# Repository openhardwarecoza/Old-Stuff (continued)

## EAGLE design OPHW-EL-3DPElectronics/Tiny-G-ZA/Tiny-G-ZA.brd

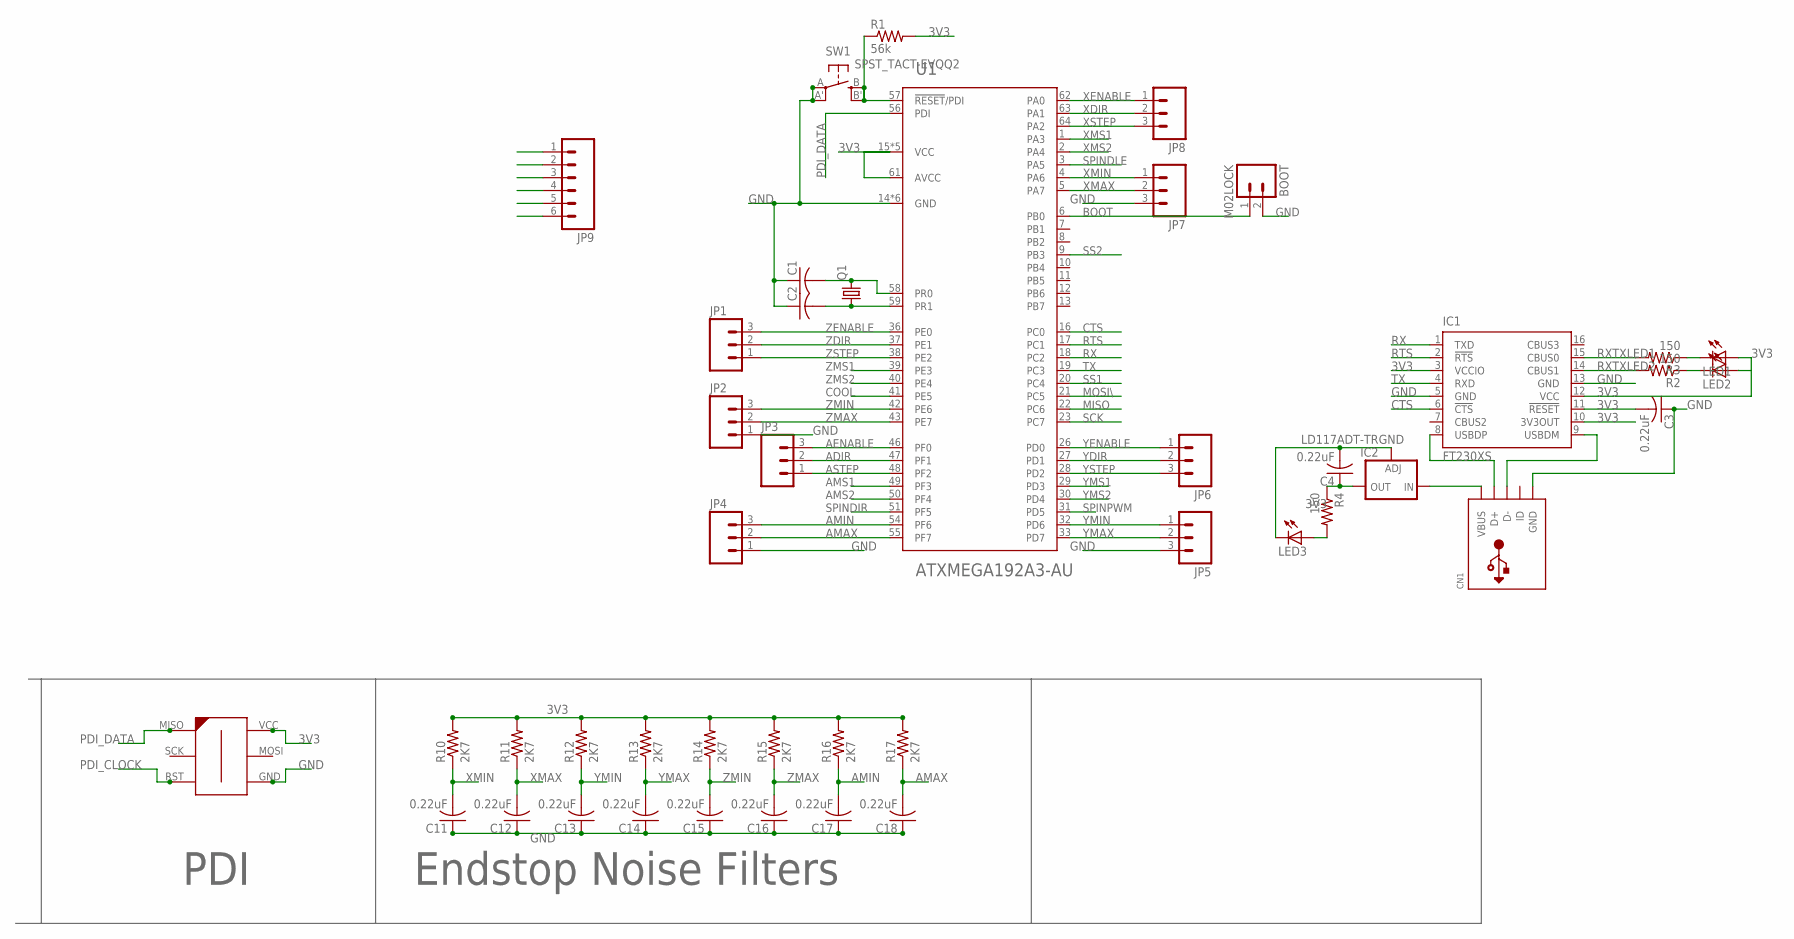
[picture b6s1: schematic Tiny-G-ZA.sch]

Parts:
BOOT: M02LOCK; 1X02_LOCK
C1, C2: C-USC1206K; C1206K
C3, C4, C11, C12, C13, C14, C15, C16, C17, C18: 0.22uF; C1206K
CN1: USBMINIB; USB-MINIB
IC1: FT230XS; SSOP16
IC2: LD117ADT-TR; DPACK
JP1, JP2, JP3, JP4, JP5, JP6, JP7, JP8: M03LONGPADS; 1X03_LONGPADS
JP9: M06LONGPADS; 1X06_LONGPADS
LED1, LED2, LED3: LEDSMT1206; 1206
Q1: CRYSTALHC49UP; HC49UP
R1: 56k; M1206
R2, R3, R4: 150; M1206
R10, R11, R12, R13, R14, R15, R16, R17: 2K7; M1206
SW1: SPST_TACT-EVQQ2; EVQ-Q2
U1: ATXMEGA192A3-AU; TQFP-64A-64
U$1: AVR-ISP-6-EDGE; 6PAD_ISP

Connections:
3V3: C3.2, C4.1, IC1.3 (VCCIO), IC1.10 (3V3OUT), IC1.11 (!RESET), IC1.12 (VCC), IC2.4 (OUT), JP9.1, LED1.A, LED2.A, R1.2, R4.1, R10.2, R11.2, R12.2, R13.2, R14.2, R15.2, R16.2, R17.2, U1.15 (VCC), U1.25 (VCC), U1.35 (VCC), U1.45 (VCC), U1.53 (VCC), U1.61 (AVCC), U$1.VCC
5V: CN1.VBUS, IC2.3 (IN)
ADIR: JP3.2, U1.47 (PF1)
AENABLE: JP3.3, U1.46 (PF0)
AMAX: C18.2, JP4.2, R17.1, U1.55 (PF7)
AMIN: C17.2, JP4.3, R16.1, U1.54 (PF6)
AMS1: U1.49 (PF3)
AMS2: U1.50 (PF4)
ASTEP: JP3.1, U1.48 (PF2)
BOOT: BOOT.1, U1.6 (PB0)
COOL: JP9.6, U1.41 (PE5)
CTS: IC1.6 (!CTS), U1.16 (PC0)
GND: BOOT.2, C1.1, C2.1, C3.1, C4.2, C11.1, C12.1, C13.1, C14.1, C15.1, C16.1, C17.1, C18.1, CN1.GND, IC1.5 (GND), IC1.13 (GND), IC2.1 (ADJ), JP2.1, JP4.1, JP5.3, JP7.3, JP9.2, LED3.C, SW1.A, SW1.A' (P1), U1.14 (GND), U1.24 (GND), U1.34 (GND), U1.44 (GND), U1.52 (GND), U1.60 (GND), U$1.GND
MISO: U1.22 (PC6)
MOSI\: U1.21 (PC5)
unnamed: CN1.D+, IC1.8 (USBDP)
unnamed: CN1.D-, IC1.9 (USBDM)
unnamed: LED3.A, R4.2
unnamed: LED2.C, R2.1
unnamed: LED1.C, R3.1
PDI_CLOCK: R1.1, SW1.B (S), SW1.B' (S1), U1.57 (!RESET!/PDI), U$1.RST
PDI_DATA: U1.56 (PDI), U$1.MISO
PR0: C1.2, Q1.2, U1.58 (PR0)
PR1: C2.2, Q1.1, U1.59 (PR1)
RTS: IC1.2 (!RTS), U1.17 (PC1)
RX: IC1.1 (TXD), U1.18 (PC2)
RXTXLED1: IC1.15 (CBUS0), R3.2
RXTXLED2: IC1.14 (CBUS1), R2.2
SCK: U1.23 (PC7)
SPINDIR: JP9.5, U1.51 (PF5)
SPINDLE: JP9.3, U1.3 (PA5)
SPINPWM: JP9.4, U1.31 (PD5)
SS1: U1.20 (PC4)
SS2: U1.9 (PB3)
TX: IC1.4 (RXD), U1.19 (PC3)
XDIR: JP8.2, U1.63 (PA1)
XENABLE: JP8.1, U1.62 (PA0)
XMAX: C12.2, JP7.2, R11.1, U1.5 (PA7)
XMIN: C11.2, JP7.1, R10.1, U1.4 (PA6)
XMS1: U1.1 (PA3)
XMS2: U1.2 (PA4)
XSTEP: JP8.3, U1.64 (PA2)
YDIR: JP6.2, U1.27 (PD1)
YENABLE: JP6.1, U1.26 (PD0)
YMAX: C14.2, JP5.2, R13.1, U1.33 (PD7)
YMIN: C13.2, JP5.1, R12.1, U1.32 (PD6)
YMS1: U1.29 (PD3)
YMS2: U1.30 (PD4)
YSTEP: JP6.3, U1.28 (PD2)
ZDIR: JP1.2, U1.37 (PE1)
ZENABLE: JP1.3, U1.36 (PE0)
ZMAX: C16.2, JP2.2, R15.1, U1.43 (PE7)
ZMIN: C15.2, JP2.3, R14.1, U1.42 (PE6)
ZMS1: U1.39 (PE3)
ZMS2: U1.40 (PE4)
ZSTEP: JP1.1, U1.38 (PE2)

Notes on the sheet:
PDI
Endstop Noise Filters

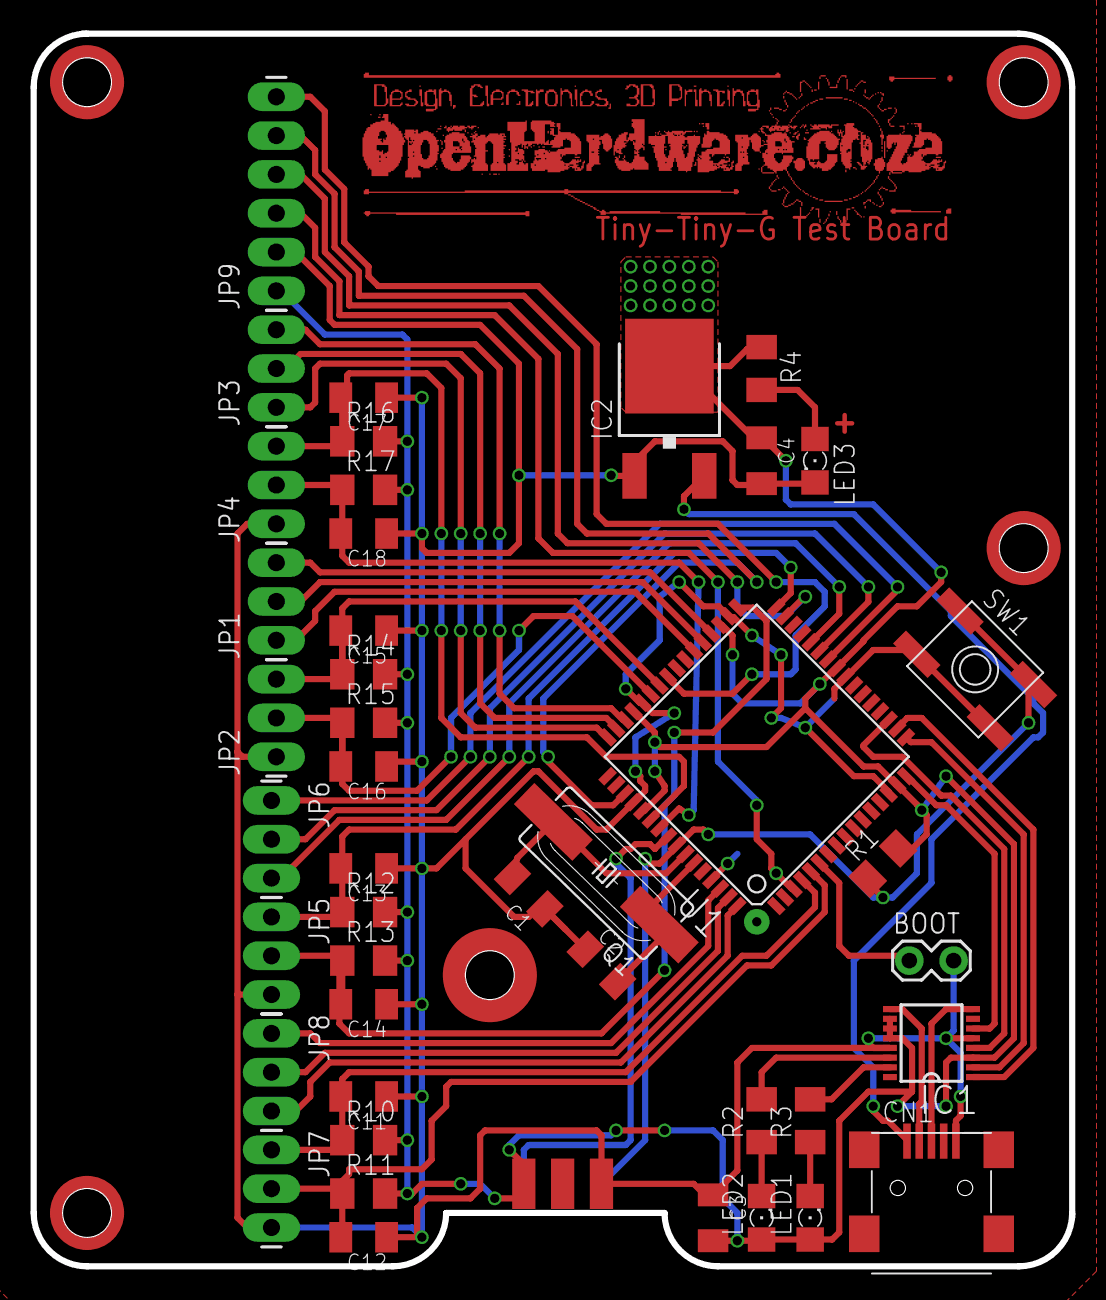
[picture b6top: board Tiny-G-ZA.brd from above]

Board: 2 copper layers, 67.9 x 80.6 mm, 44 parts (1 on the bottom side), 43 nets.
